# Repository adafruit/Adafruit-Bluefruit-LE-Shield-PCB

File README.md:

## Adafruit Bluefruit LE Shield PCB
<a href="http://www.adafruit.com/products/2746"><br/>
Click here to purchase one from the Adafruit shop</a>

Would you like to add powerful and easy-to-use Bluetooth Low Energy to your robot, art or other electronics project? Heck yeah! With BLE now included in modern smart phones and tablets, its fun to add wireless connectivity. So what you really need is the new Adafruit Bluefruit LE Shield for Arduino!

The Bluefruit LE Shield makes it easy to add Bluetooth Low Energy connectivity to your Arduino or compatible.  Solder in the included headers and plug right in. It connects to your Arduino or other microcontroller using the hardware SPI interface (MISO, MOSI, SCK) plus a chip select line (default D8), interrupt line (default D7) and reset (default D4). You can rearrange any and all the pins if you'd like, by cutting the jumpers underneath, and soldering jumper wires to your desired pins.

PCB files for the Adafruit Bluefruit LE Shield. The format is EagleCAD schematic and board layout
- https://www.adafruit.com/product/2746

### License

Adafruit invests time and resources providing this open source design, please support Adafruit and open-source hardware by purchasing products from [Adafruit](https://www.adafruit.com)!

All text above must be included in any redistribution

Designed by Limor Fried/Ladyada for Adafruit Industries.
Creative Commons Attribution/Share-Alike, all text above must be included in any redistribution. 
See license.txt for additional information.

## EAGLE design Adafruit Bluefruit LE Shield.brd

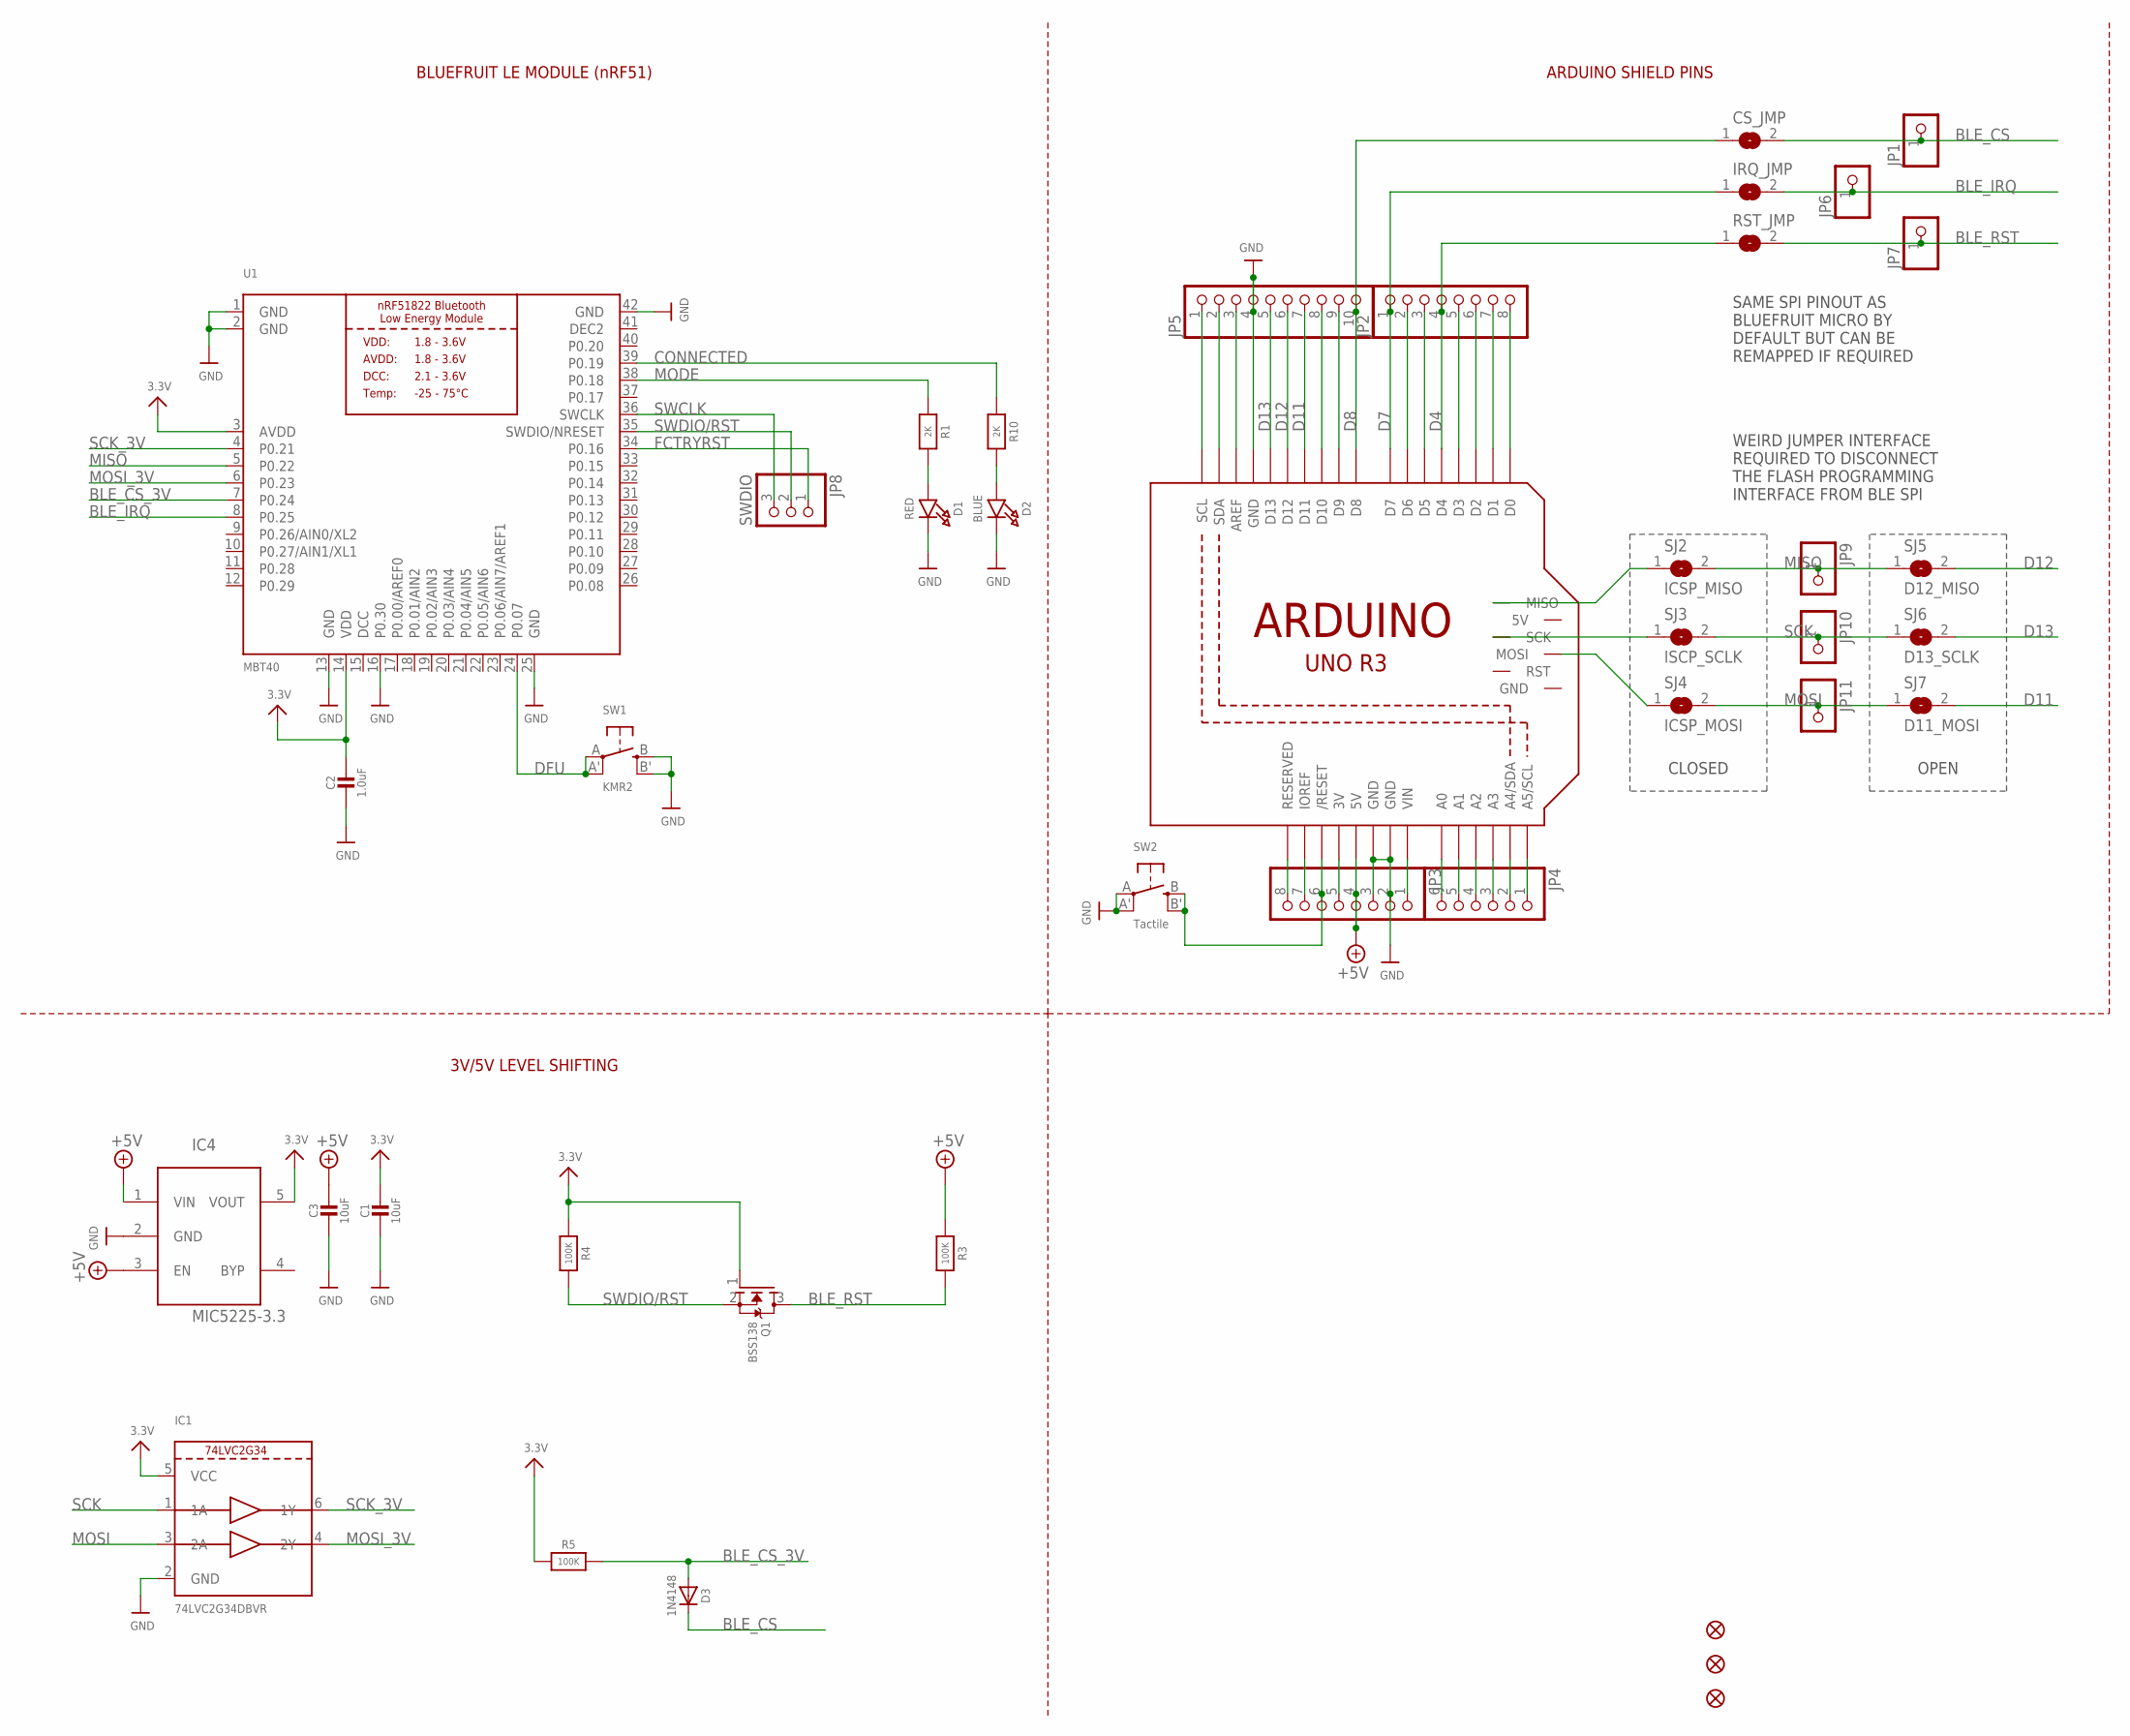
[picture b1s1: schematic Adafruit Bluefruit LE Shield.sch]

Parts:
C1, C3: 10uF; 0805-NO
C2: 1.0uF; 0805-NO
CS_JMP: SOLDERJUMPERCLOSED; SOLDERJUMPER_CLOSEDWIRE
D1: RED; CHIPLED_0805_NOOUTLINE
D2: BLUE; CHIPLED_0805_NOOUTLINE
D3: 1N4148; SOD-323
FID1, FID2, FID3: FIDUCIAL""; FIDUCIAL_1MM
IC1: 74LVC2G34DBVR; SOT23-6
IC4: MIC5225-3.3; SOT23-5L
IRQ_JMP: SOLDERJUMPERCLOSED; SOLDERJUMPER_CLOSEDWIRE
JP1, JP6, JP7, JP9, JP10, JP11: HEADER-1X1ROUND; 1X01_ROUND
JP2, JP3: HEADER-1X870MIL; 1X08_ROUND_70
JP4: HEADER-1X670MIL; 1X06_ROUND_70
JP5: HEADER-1X1070MIL; 1X10_ROUND70
JP8: SWDIO; 1X03_ROUND_76
M1: ARDUINO_R3_ICSP_NODIM; ARDUINOR3_ICSP_NODIM
Q1: BSS138; SOT23-WIDE
R1, R10: 2K; 0805-NO
R3, R4, R5: 100K; 0805-NO
RST_JMP: SOLDERJUMPERCLOSED; SOLDERJUMPER_CLOSEDWIRE
SJ2: ICSP_MISO; SOLDERJUMPER_CLOSEDWIRE
SJ3: ISCP_SCLK; SOLDERJUMPER_CLOSEDWIRE
SJ4: ICSP_MOSI; SOLDERJUMPER_CLOSEDWIRE
SJ5: D12_MISO; SOLDERJUMPER_REFLOW_NOPASTE
SJ6: D13_SCLK; SOLDERJUMPER_REFLOW_NOPASTE
SJ7: D11_MOSI; SOLDERJUMPER_REFLOW_NOPASTE
SW1: KMR2; BTN_KMR2_4.6X2.8
SW2: Tactile; EVQ-Q2
U1: MBT40; BLE_MODULE_RAYTAC_MDBT40

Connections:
3.3V: C1.1, C2.1, IC1.5 (VCC), IC4.5 (VOUT), Q1.1 (G), R4.1, R5.1, U1.3 (AVDD), U1.14 (VDD)
+3V: JP3.5, M1.3V
+5V: C3.1, IC4.1 (VIN), IC4.3 (EN), JP3.4, M1.5V, R3.1
A0: JP4.6, M1.A0
A1: JP4.5, M1.A1
A2: JP4.4, M1.A2
A3: JP4.3, M1.A3
A4: JP4.2, M1.A4 (A4/SDA)
A5: JP4.1, M1.A5 (A5/SCL)
AREF: JP5.3, M1.AREF
BLE_CS: CS_JMP.2, D3.C, JP1.1
BLE_CS_3V: D3.A, R5.2, U1.7 (P0.24)
BLE_IRQ: IRQ_JMP.2, JP6.1, U1.8 (P0.25)
BLE_RST: JP7.1, Q1.3 (D), R3.2, RST_JMP.2
CONNECTED: R10.1, U1.39 (P0.19)
D4: JP2.4, M1.D4, RST_JMP.1
D7: IRQ_JMP.1, JP2.1, M1.D7
D8: CS_JMP.1, JP5.10, M1.D8
D11: JP5.7, M1.D11, SJ7.2
D12: JP5.6, M1.D12, SJ5.2
D13: JP5.5, M1.D13, SJ6.2
DCC: U1.15 (DCC)
DEC2: U1.41 (DEC2)
DFU: SW1.A, SW1.A' (P1), U1.24 (P0.07)
FCTRYRST: JP8.1, U1.34 (P0.16)
GND: C1.2, C2.2, C3.2, D1.C, D2.C, IC1.2 (GND), IC4.2 (GND), JP3.2, JP3.3, JP5.4, M1.GND, M1.GND@1 (GND), M1.GND@3 (GND), SW1.B (S), SW1.B' (S1), SW2.A, SW2.A' (P1), U1.1 (GND), U1.2 (GND), U1.13 (GND), U1.16 (P0.30), U1.25 (GND), U1.42 (GND)
IOREF: JP3.7, M1.IOREF
MISO: JP9.1, SJ2.2, SJ5.1, U1.5 (P0.22)
MISO_ICSP: M1.MISO, SJ2.1
MODE: R1.1, U1.38 (P0.18)
MOSI: IC1.3 (2A), JP11.1, SJ4.2, SJ7.1
MOSI_3V: IC1.4 (2Y), U1.6 (P0.23)
MOSI_ICSP: M1.MOSI, SJ4.1
unnamed: D1.A, R1.2
unnamed: D2.A, R10.2
unnamed: JP2.2, M1.D6
unnamed: JP2.3, M1.D5
unnamed: JP2.5, M1.D3
unnamed: JP2.6, M1.D2
unnamed: JP2.7, M1.D1
unnamed: JP2.8, M1.D0
unnamed: JP5.8, M1.D10
unnamed: JP5.9, M1.D9
NC: JP3.8, M1.RESERVED
RESET: JP3.6, M1.RESET (/RESET), SW2.B (S), SW2.B' (S1)
SCK: IC1.1 (1A), JP10.1, SJ3.2, SJ6.1
SCK_3V: IC1.6 (1Y), U1.4 (P0.21)
SCK_ICSP: M1.SCK, SJ3.1
SCL: JP5.1, M1.SCL
SDA: JP5.2, M1.SDA
SWCLK: JP8.3, U1.36 (SWCLK)
SWDIO/RST: JP8.2, Q1.2 (S), R4.2, U1.35 (SWDIO/NRESET)
VIN: JP3.1, M1.VIN

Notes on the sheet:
ARDUINO SHIELD PINS
BLUEFRUIT LE MODULE (nRF51)
WEIRD JUMPER INTERFACE REQUIRED TO DISCONNECT THE FLASH PROGRAMMING INTERFACE FROM BLE SPI
CLOSED
OPEN
3V/5V LEVEL SHIFTING
SAME SPI PINOUT AS BLUEFRUIT MICRO BY DEFAULT BUT CAN BE REMAPPED IF REQUIRED

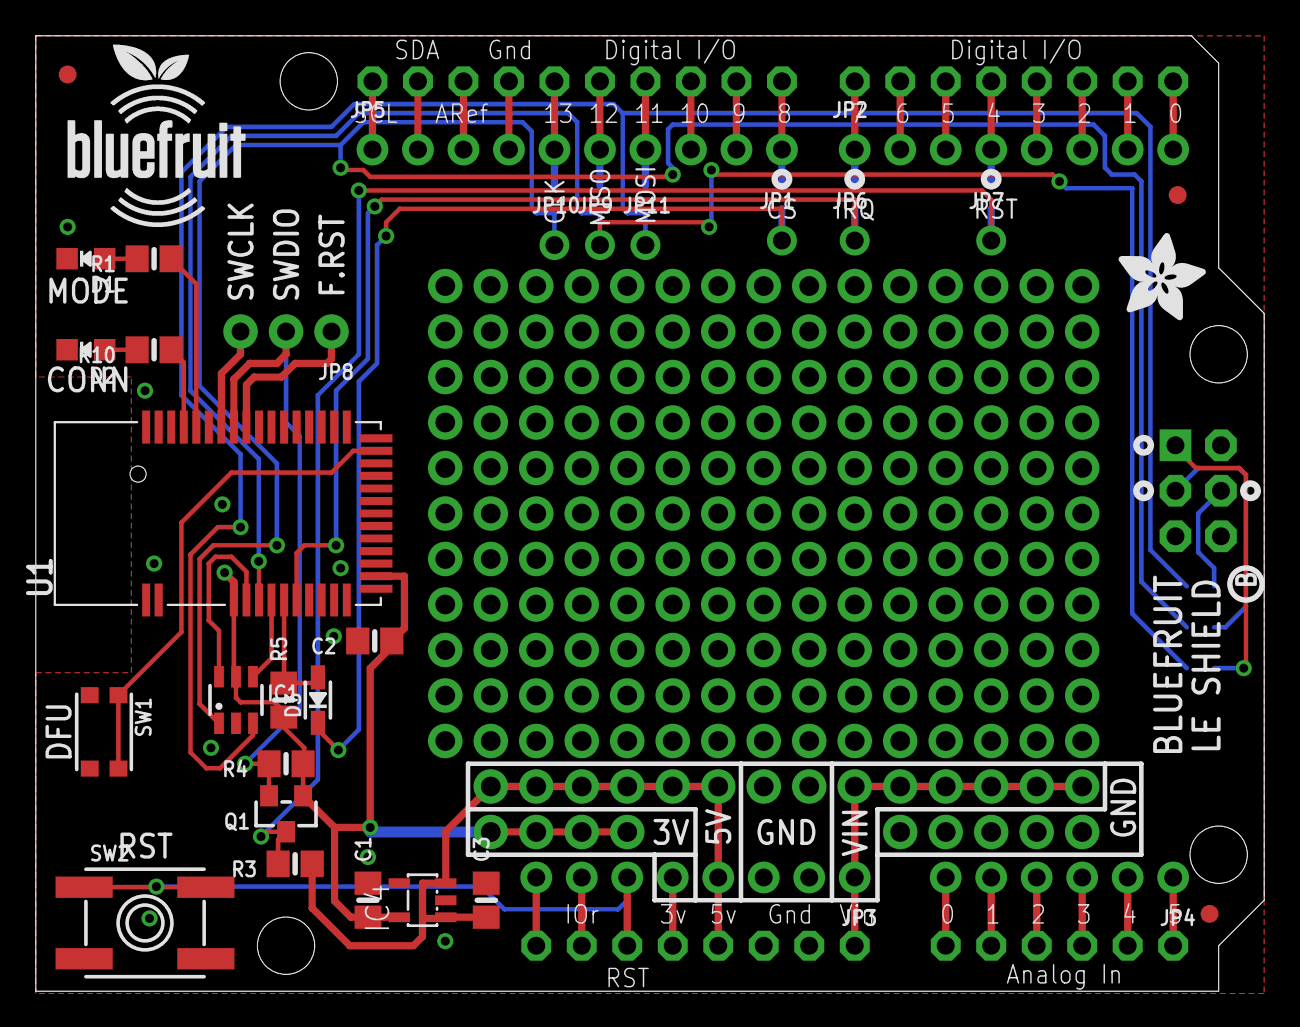
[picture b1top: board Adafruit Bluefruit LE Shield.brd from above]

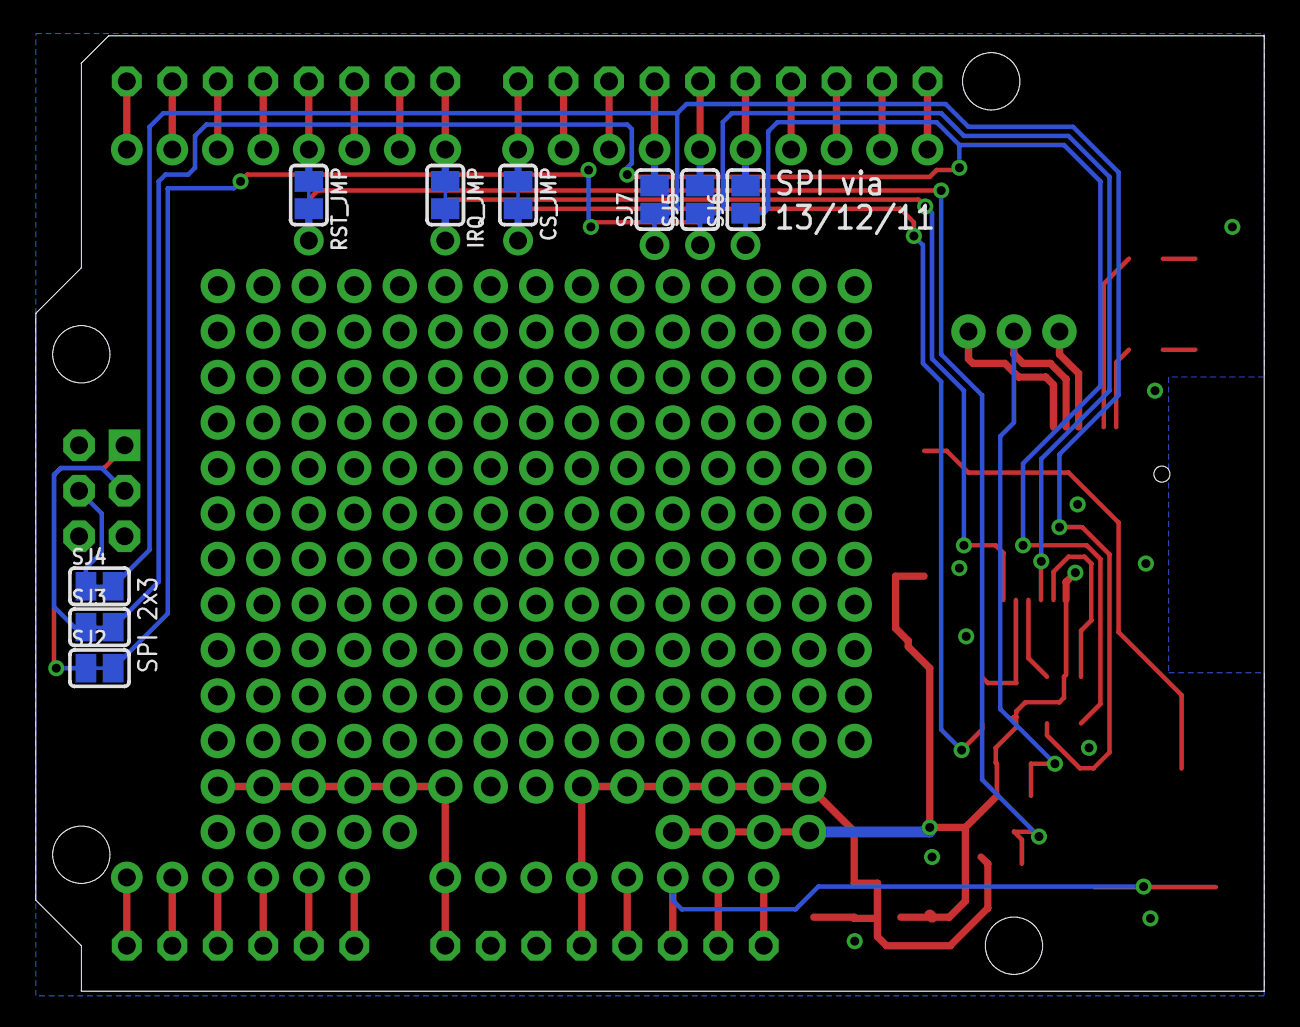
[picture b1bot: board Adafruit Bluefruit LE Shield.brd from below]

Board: 2 copper layers, 68.6 x 53.3 mm, 44 parts (9 on the bottom side), 51 nets.

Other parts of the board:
U$8: BLUEFRUITLOGO_100MM
U$9: ADAFRUIT_5MM
U$21: PCBFEAT-REV-040

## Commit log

2016-09-21 init

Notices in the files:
parts and their libraries:
microbuilder: This work is placed in the public domain, and may be freely used for commercial and non-commercial work with the following conditions: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
